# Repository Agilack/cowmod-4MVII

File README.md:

# Cowmod
Cowmod is a family of development boards to help quick prototyping using a
main board and a set of modules. The 4MVII board is focused on PMODs modules
form-factor and offer 4 PMOD connectors to connect extensions.

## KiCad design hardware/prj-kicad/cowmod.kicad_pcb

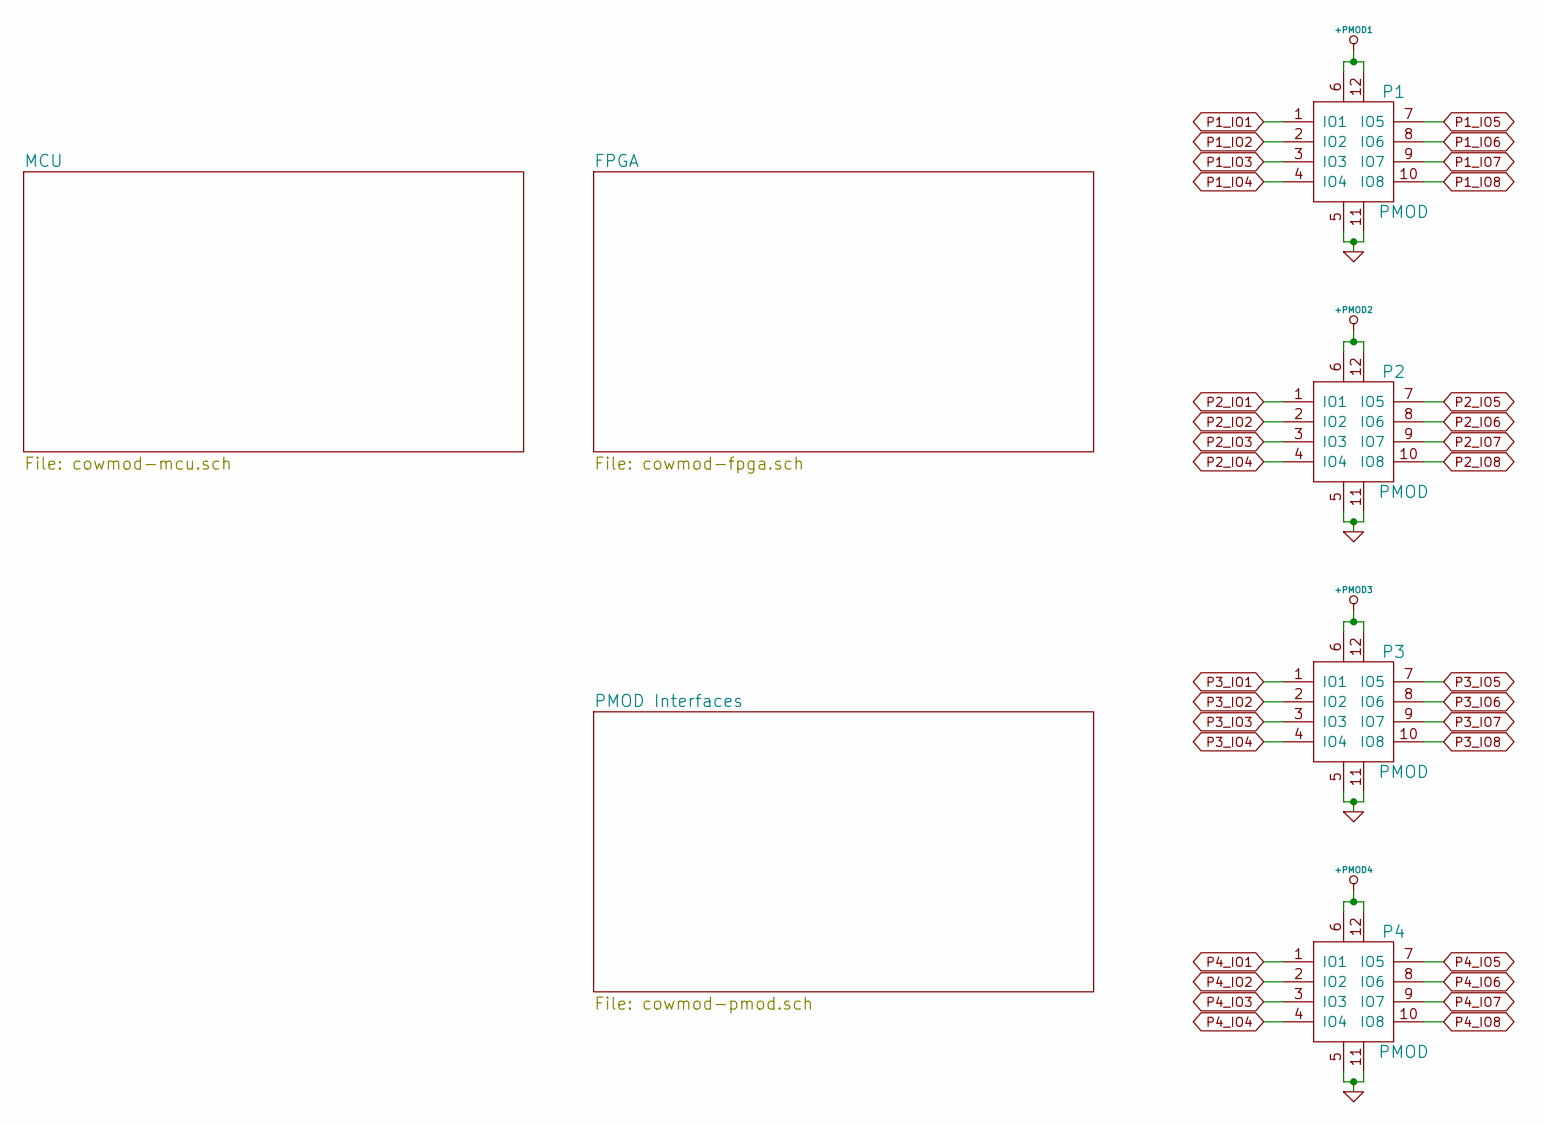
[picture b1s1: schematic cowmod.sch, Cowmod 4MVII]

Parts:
P1, P2, P3, P4: PMOD; PMOD_SSW106-RA

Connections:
+PMOD1: P1.6, P1.12; also elsewhere on the board
+PMOD2: P2.6, P2.12; also elsewhere on the board
+PMOD3: P3.6, P3.12; also elsewhere on the board
+PMOD4: P4.6, P4.12; also elsewhere on the board
GND: P1.5, P1.11, P2.5, P2.11, P3.5, P3.11, P4.5, P4.11; also elsewhere on the board
P1_IO1: P1.1 (IO1); also elsewhere on the board
P1_IO2: P1.2 (IO2); also elsewhere on the board
P1_IO3: P1.3 (IO3); also elsewhere on the board
P1_IO4: P1.4 (IO4); also elsewhere on the board
P1_IO5: P1.7 (IO5); also elsewhere on the board
P1_IO6: P1.8 (IO6); also elsewhere on the board
P1_IO7: P1.9 (IO7); also elsewhere on the board
P1_IO8: P1.10 (IO8); also elsewhere on the board
P2_IO1: P2.1 (IO1); also elsewhere on the board
P2_IO2: P2.2 (IO2); also elsewhere on the board
P2_IO3: P2.3 (IO3); also elsewhere on the board
P2_IO4: P2.4 (IO4); also elsewhere on the board
P2_IO5: P2.7 (IO5); also elsewhere on the board
P2_IO6: P2.8 (IO6); also elsewhere on the board
P2_IO7: P2.9 (IO7); also elsewhere on the board
P2_IO8: P2.10 (IO8); also elsewhere on the board
P3_IO1: P3.1 (IO1); also elsewhere on the board
P3_IO2: P3.2 (IO2); also elsewhere on the board
P3_IO3: P3.3 (IO3); also elsewhere on the board
P3_IO4: P3.4 (IO4); also elsewhere on the board
P3_IO5: P3.7 (IO5); also elsewhere on the board
P3_IO6: P3.8 (IO6); also elsewhere on the board
P3_IO7: P3.9 (IO7); also elsewhere on the board
P3_IO8: P3.10 (IO8); also elsewhere on the board
P4_IO1: P4.1 (IO1); also elsewhere on the board
P4_IO2: P4.2 (IO2); also elsewhere on the board
P4_IO3: P4.3 (IO3); also elsewhere on the board
P4_IO4: P4.4 (IO4); also elsewhere on the board
P4_IO5: P4.7 (IO5); also elsewhere on the board
P4_IO6: P4.8 (IO6); also elsewhere on the board
P4_IO7: P4.9 (IO7); also elsewhere on the board
P4_IO8: P4.10 (IO8); also elsewhere on the board

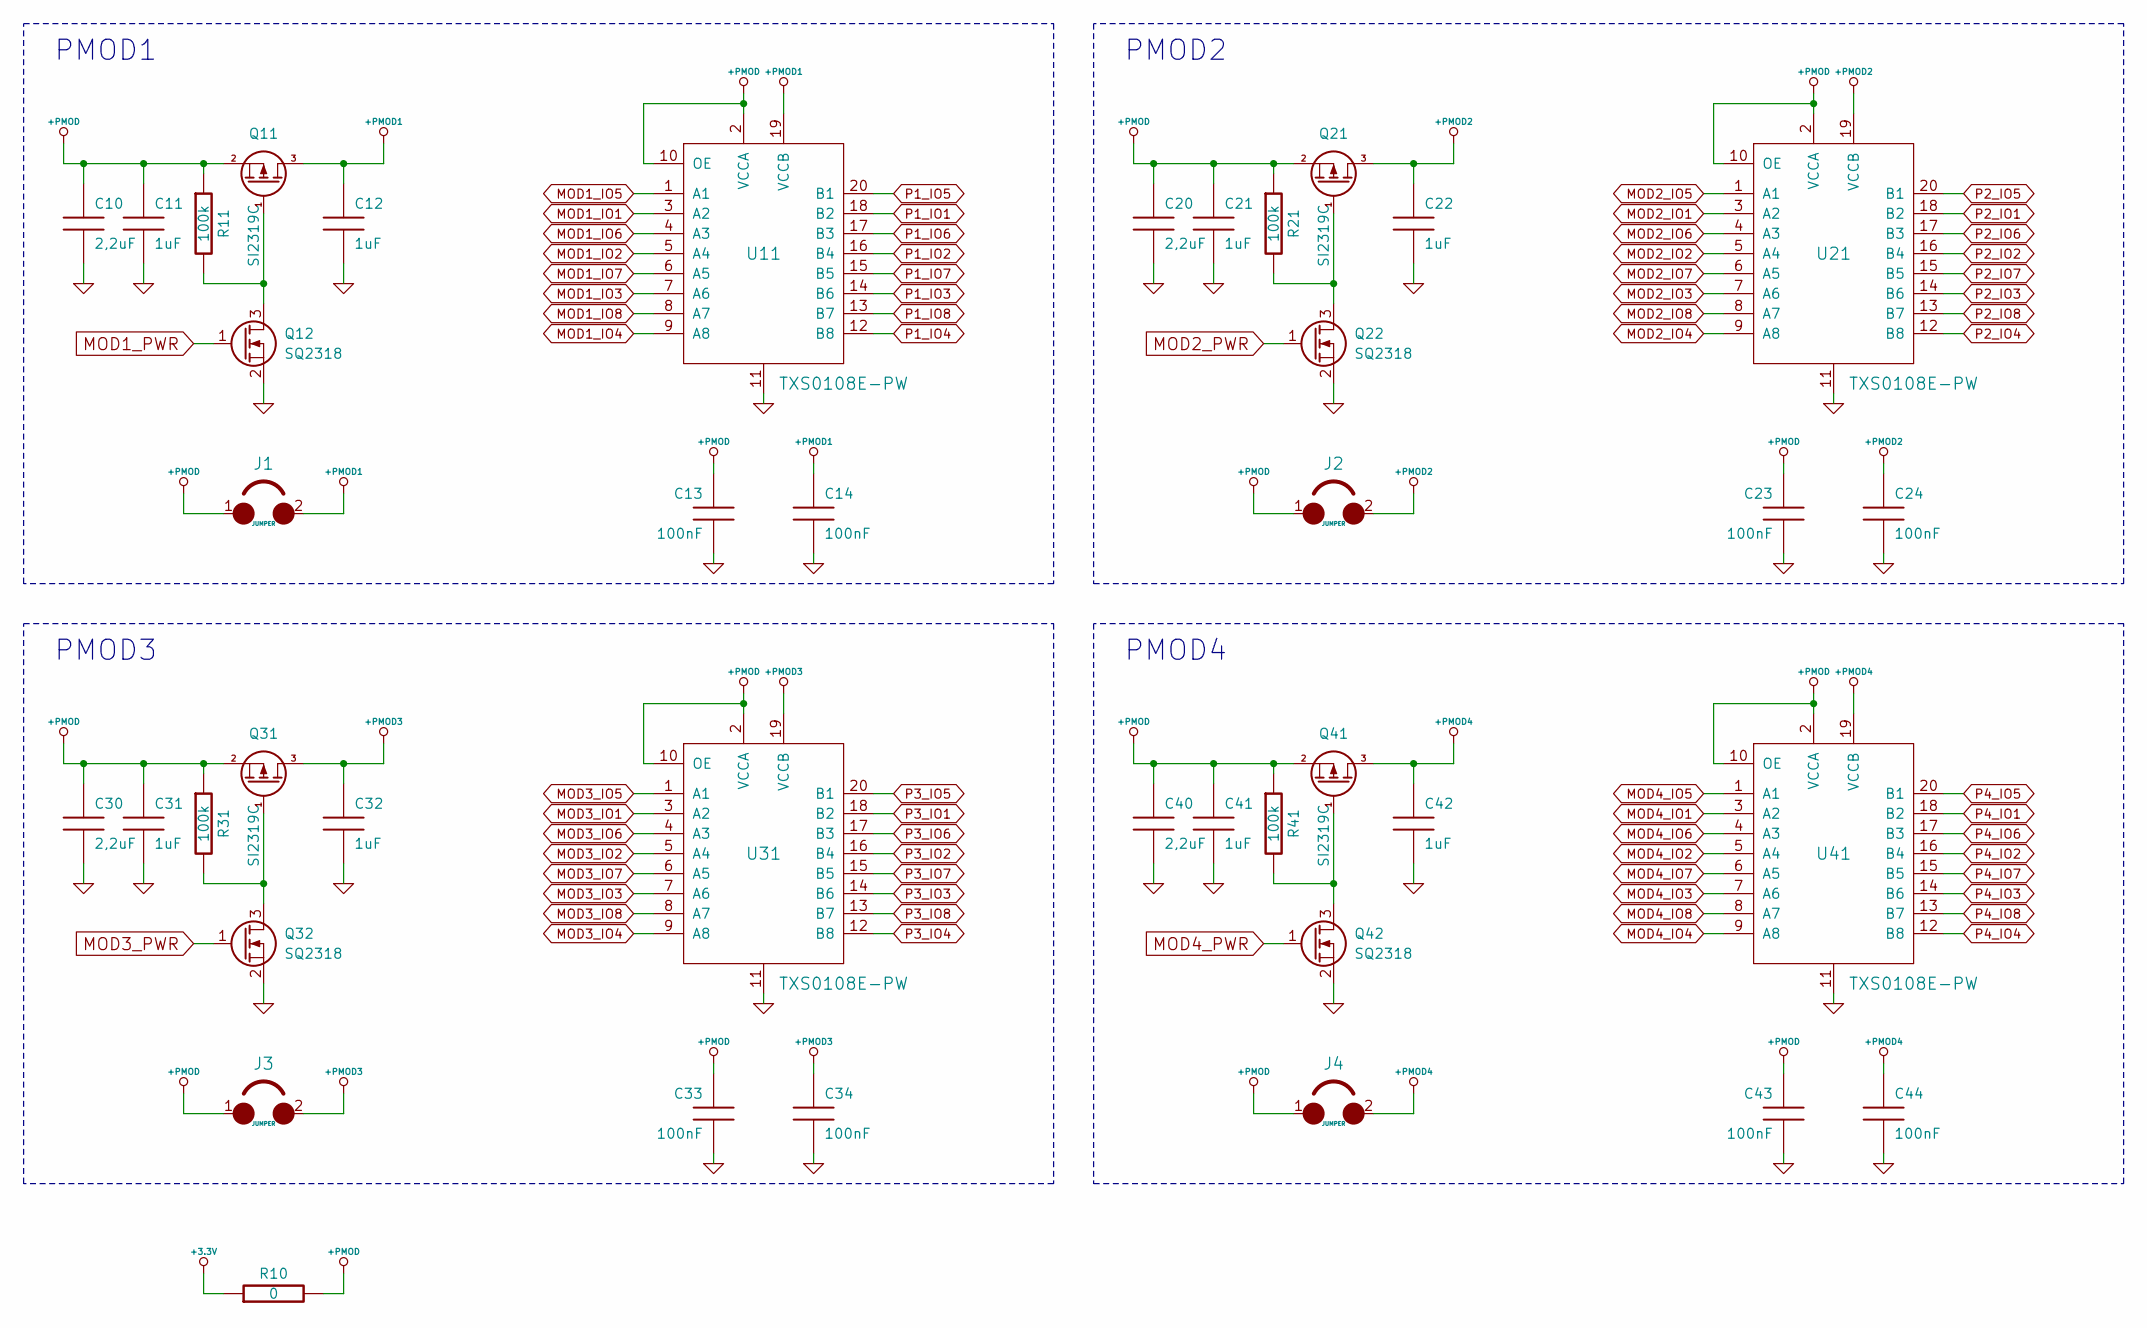
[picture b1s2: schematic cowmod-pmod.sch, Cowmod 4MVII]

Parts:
C10, C20, C30, C40: 2,2uF; SMD1210
C11, C21, C31, C41: 1uF; SMD0603
C12, C22, C32, C42: 1uF; SMD0805
C13, C14, C23, C24, C33, C34, C43, C44: 100nF; SMD0603
J1, J2, J3, J4: JUMPER; CONN_2
Q11, Q21, Q31, Q41: SI2319C; SOT23-3
Q12, Q22, Q32, Q42: SQ2318; SOT23-3
R10: 0; SMD0805
R11, R21, R31, R41: 100k; SMD0603
U11, U21, U31, U41: TXS0108E-PW; TSSOP20

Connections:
+3.3V: R10.1; also elsewhere on the board
+PMOD: C10.1, C11.1, C13.1, C20.1, C21.1, C23.1, C30.1, C31.1, C33.1, C40.1, C41.1, C43.1, J1.1, J2.1, J3.1, J4.1, Q11.2 (S), Q21.2 (S), Q31.2 (S), Q41.2 (S), R10.2, R11.1, R21.1, R31.1, R41.1, U11.2 (VCCA), U11.10 (OE), U21.2 (VCCA), U21.10 (OE), U31.2 (VCCA), U31.10 (OE), U41.2 (VCCA), U41.10 (OE); also elsewhere on the board
+PMOD1: C12.1, C14.1, J1.2, Q11.3 (D), U11.19 (VCCB); also elsewhere on the board
+PMOD2: C22.1, C24.1, J2.2, Q21.3 (D), U21.19 (VCCB); also elsewhere on the board
+PMOD3: C32.1, C34.1, J3.2, Q31.3 (D), U31.19 (VCCB); also elsewhere on the board
+PMOD4: C42.1, C44.1, J4.2, Q41.3 (D), U41.19 (VCCB); also elsewhere on the board
GND: C10.2, C11.2, C12.2, C13.2, C14.2, C20.2, C21.2, C22.2, C23.2, C24.2, C30.2, C31.2, C32.2, C33.2, C34.2, C40.2, C41.2, C42.2, C43.2, C44.2, Q12.2 (S), Q22.2 (S), Q32.2 (S), Q42.2 (S), U11.11, U21.11, U31.11, U41.11; also elsewhere on the board
MOD1_IO1: U11.3 (A2); also elsewhere on the board
MOD1_IO2: U11.5 (A4); also elsewhere on the board
MOD1_IO3: U11.7 (A6); also elsewhere on the board
MOD1_IO4: U11.9 (A8); also elsewhere on the board
MOD1_IO5: U11.1 (A1); also elsewhere on the board
MOD1_IO6: U11.4 (A3); also elsewhere on the board
MOD1_IO7: U11.6 (A5); also elsewhere on the board
MOD1_IO8: U11.8 (A7); also elsewhere on the board
MOD1_PWR: Q12.1 (G)
MOD2_IO1: U21.3 (A2); also elsewhere on the board
MOD2_IO2: U21.5 (A4); also elsewhere on the board
MOD2_IO3: U21.7 (A6); also elsewhere on the board
MOD2_IO4: U21.9 (A8); also elsewhere on the board
MOD2_IO5: U21.1 (A1); also elsewhere on the board
MOD2_IO6: U21.4 (A3); also elsewhere on the board
MOD2_IO7: U21.6 (A5); also elsewhere on the board
MOD2_IO8: U21.8 (A7); also elsewhere on the board
MOD2_PWR: Q22.1 (G)
MOD3_IO1: U31.3 (A2); also elsewhere on the board
MOD3_IO2: U31.5 (A4); also elsewhere on the board
MOD3_IO3: U31.7 (A6); also elsewhere on the board
MOD3_IO4: U31.9 (A8); also elsewhere on the board
MOD3_IO5: U31.1 (A1); also elsewhere on the board
MOD3_IO6: U31.4 (A3); also elsewhere on the board
MOD3_IO7: U31.6 (A5); also elsewhere on the board
MOD3_IO8: U31.8 (A7); also elsewhere on the board
MOD3_PWR: Q32.1 (G)
MOD4_IO1: U41.3 (A2); also elsewhere on the board
MOD4_IO2: U41.5 (A4); also elsewhere on the board
MOD4_IO3: U41.7 (A6); also elsewhere on the board
MOD4_IO4: U41.9 (A8); also elsewhere on the board
MOD4_IO5: U41.1 (A1); also elsewhere on the board
MOD4_IO6: U41.4 (A3); also elsewhere on the board
MOD4_IO7: U41.6 (A5); also elsewhere on the board
MOD4_IO8: U41.8 (A7); also elsewhere on the board
MOD4_PWR: Q42.1 (G)
unnamed: Q11.1 (G), Q12.3 (D), R11.2
unnamed: Q21.1 (G), Q22.3 (D), R21.2
unnamed: Q31.1 (G), Q32.3 (D), R31.2
unnamed: Q41.1 (G), Q42.3 (D), R41.2
P1_IO1: U11.18 (B2); also elsewhere on the board
P1_IO2: U11.16 (B4); also elsewhere on the board
P1_IO3: U11.14 (B6); also elsewhere on the board
P1_IO4: U11.12 (B8); also elsewhere on the board
P1_IO5: U11.20 (B1); also elsewhere on the board
P1_IO6: U11.17 (B3); also elsewhere on the board
P1_IO7: U11.15 (B5); also elsewhere on the board
P1_IO8: U11.13 (B7); also elsewhere on the board
P2_IO1: U21.18 (B2); also elsewhere on the board
P2_IO2: U21.16 (B4); also elsewhere on the board
P2_IO3: U21.14 (B6); also elsewhere on the board
P2_IO4: U21.12 (B8); also elsewhere on the board
P2_IO5: U21.20 (B1); also elsewhere on the board
P2_IO6: U21.17 (B3); also elsewhere on the board
P2_IO7: U21.15 (B5); also elsewhere on the board
P2_IO8: U21.13 (B7); also elsewhere on the board
P3_IO1: U31.18 (B2); also elsewhere on the board
P3_IO2: U31.16 (B4); also elsewhere on the board
P3_IO3: U31.14 (B6); also elsewhere on the board
P3_IO4: U31.12 (B8); also elsewhere on the board
P3_IO5: U31.20 (B1); also elsewhere on the board
P3_IO6: U31.17 (B3); also elsewhere on the board
P3_IO7: U31.15 (B5); also elsewhere on the board
P3_IO8: U31.13 (B7); also elsewhere on the board
P4_IO1: U41.18 (B2); also elsewhere on the board
P4_IO2: U41.16 (B4); also elsewhere on the board
P4_IO3: U41.14 (B6); also elsewhere on the board
P4_IO4: U41.12 (B8); also elsewhere on the board
P4_IO5: U41.20 (B1); also elsewhere on the board
P4_IO6: U41.17 (B3); also elsewhere on the board
P4_IO7: U41.15 (B5); also elsewhere on the board
P4_IO8: U41.13 (B7); also elsewhere on the board

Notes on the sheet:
PMOD1
PMOD2
PMOD3
PMOD4

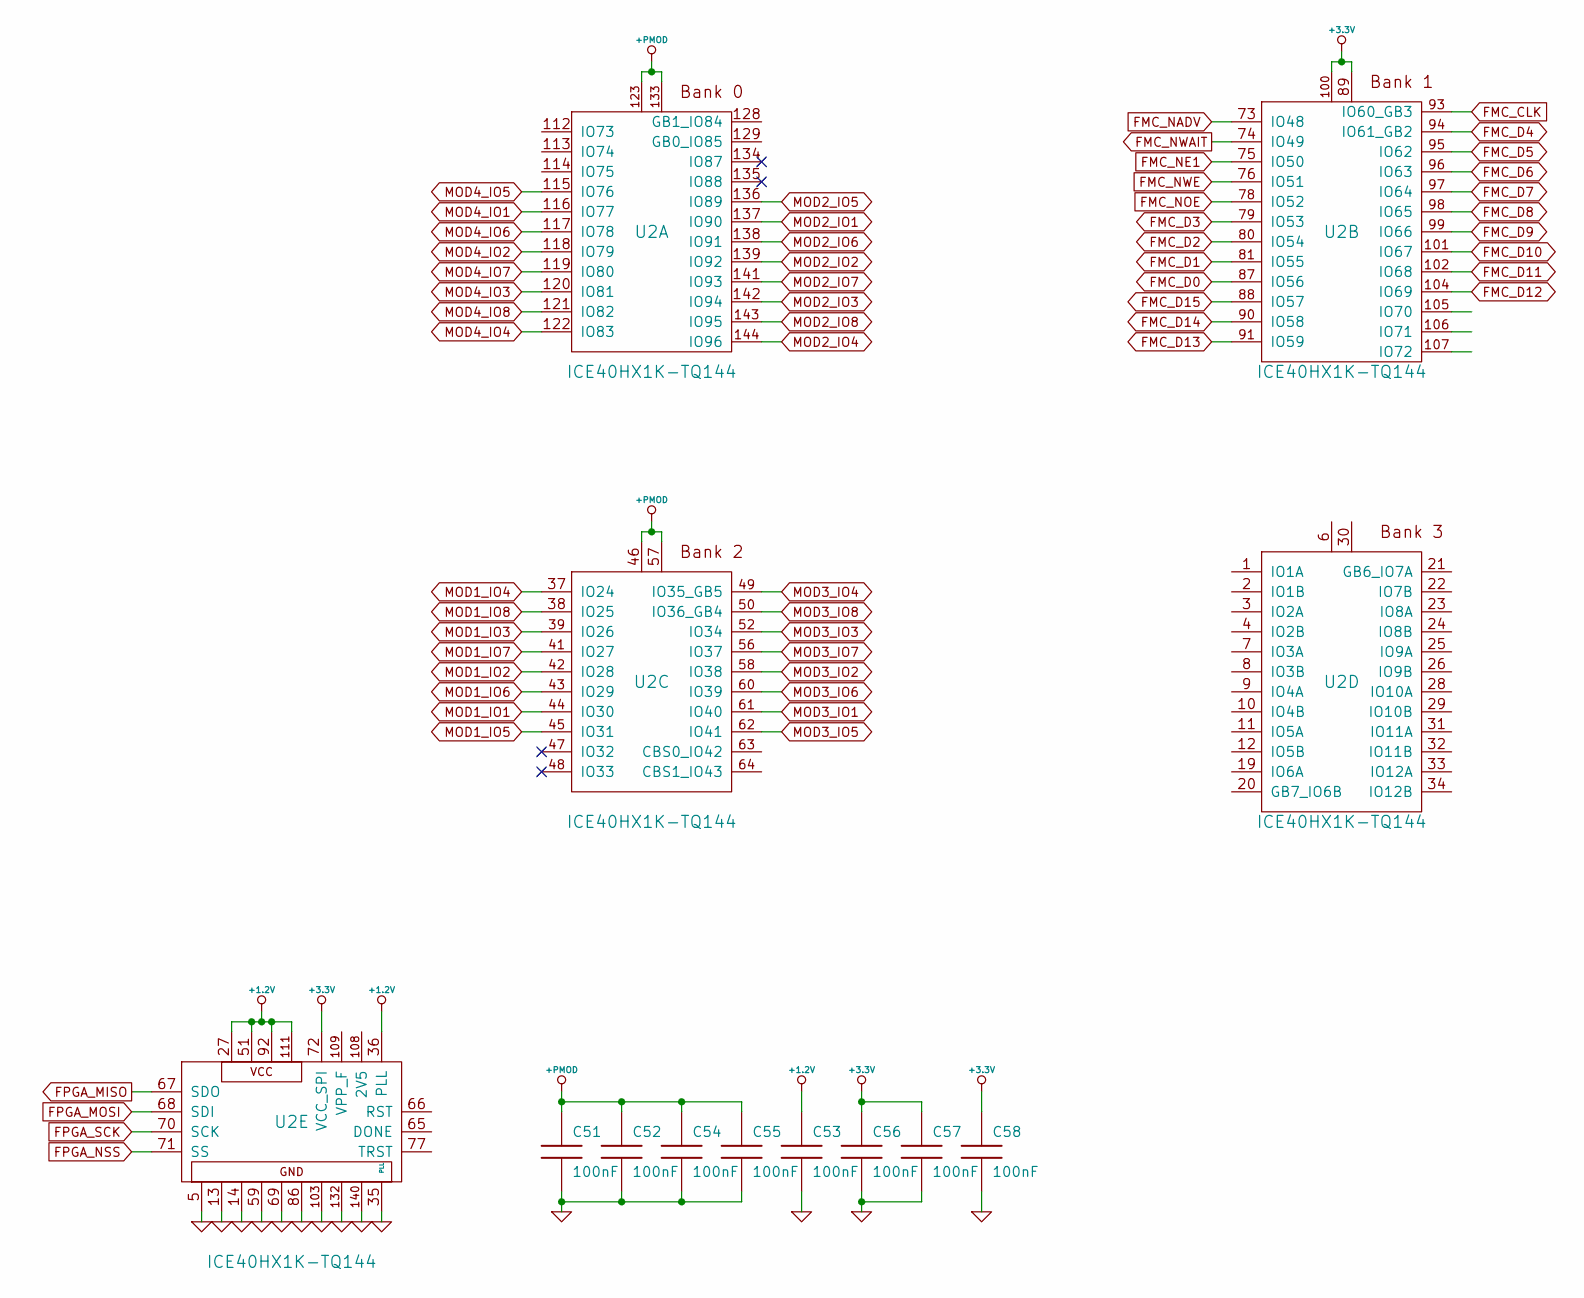
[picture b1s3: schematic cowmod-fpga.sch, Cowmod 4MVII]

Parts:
C51, C52, C53, C54, C55, C56, C57, C58: 100nF; SMD0603
U2: ICE40HX1K-TQ144; TQFP144

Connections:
+1.2V: C53.1, U2.27, U2.36 (PLL), U2.51, U2.92, U2.111
+3.3V: C56.1, C57.1, C58.1, U2.72 (VCC_SPI), U2.89, U2.100; also elsewhere on the board
+PMOD: C51.1, C52.1, C54.1, C55.1, U2.46, U2.57, U2.123, U2.133; also elsewhere on the board
FMC_CLK: U2.93 (IO60_GB3); also elsewhere on the board
FMC_D0: U2.87 (IO56); also elsewhere on the board
FMC_D1: U2.81 (IO55); also elsewhere on the board
FMC_D2: U2.80 (IO54); also elsewhere on the board
FMC_D3: U2.79 (IO53); also elsewhere on the board
FMC_D4: U2.94 (IO61_GB2); also elsewhere on the board
FMC_D5: U2.95 (IO62); also elsewhere on the board
FMC_D6: U2.96 (IO63); also elsewhere on the board
FMC_D7: U2.97 (IO64); also elsewhere on the board
FMC_D8: U2.98 (IO65); also elsewhere on the board
FMC_D9: U2.99 (IO66); also elsewhere on the board
FMC_D10: U2.101 (IO67); also elsewhere on the board
FMC_D11: U2.102 (IO68); also elsewhere on the board
FMC_D12: U2.104 (IO69); also elsewhere on the board
FMC_D13: U2.91 (IO59); also elsewhere on the board
FMC_D14: U2.90 (IO58); also elsewhere on the board
FMC_D15: U2.88 (IO57); also elsewhere on the board
FMC_NADV: U2.73 (IO48); also elsewhere on the board
FMC_NE1: U2.75 (IO50); also elsewhere on the board
FMC_NOE: U2.78 (IO52); also elsewhere on the board
FMC_NWAIT: U2.74 (IO49); also elsewhere on the board
FMC_NWE: U2.76 (IO51); also elsewhere on the board
FPGA_MISO: U2.67 (SDO); also elsewhere on the board
FPGA_MOSI: U2.68 (SDI); also elsewhere on the board
FPGA_NSS: U2.71 (SS); also elsewhere on the board
FPGA_SCK: U2.70 (SCK); also elsewhere on the board
GND: C51.2, C52.2, C53.2, C54.2, C55.2, C56.2, C57.2, C58.2, U2.5, U2.13, U2.14, U2.35 (PLL), U2.59, U2.69, U2.86, U2.103, U2.132, U2.140; also elsewhere on the board
MOD1_IO1: U2.44 (IO30); also elsewhere on the board
MOD1_IO2: U2.42 (IO28); also elsewhere on the board
MOD1_IO3: U2.39 (IO26); also elsewhere on the board
MOD1_IO4: U2.37 (IO24); also elsewhere on the board
MOD1_IO5: U2.45 (IO31); also elsewhere on the board
MOD1_IO6: U2.43 (IO29); also elsewhere on the board
MOD1_IO7: U2.41 (IO27); also elsewhere on the board
MOD1_IO8: U2.38 (IO25); also elsewhere on the board
MOD2_IO1: U2.137 (IO90); also elsewhere on the board
MOD2_IO2: U2.139 (IO92); also elsewhere on the board
MOD2_IO3: U2.142 (IO94); also elsewhere on the board
MOD2_IO4: U2.144 (IO96); also elsewhere on the board
MOD2_IO5: U2.136 (IO89); also elsewhere on the board
MOD2_IO6: U2.138 (IO91); also elsewhere on the board
MOD2_IO7: U2.141 (IO93); also elsewhere on the board
MOD2_IO8: U2.143 (IO95); also elsewhere on the board
MOD3_IO1: U2.61 (IO40); also elsewhere on the board
MOD3_IO2: U2.58 (IO38); also elsewhere on the board
MOD3_IO3: U2.52 (IO34); also elsewhere on the board
MOD3_IO4: U2.49 (IO35_GB5); also elsewhere on the board
MOD3_IO5: U2.62 (IO41); also elsewhere on the board
MOD3_IO6: U2.60 (IO39); also elsewhere on the board
MOD3_IO7: U2.56 (IO37); also elsewhere on the board
MOD3_IO8: U2.50 (IO36_GB4); also elsewhere on the board
MOD4_IO1: U2.116 (IO77); also elsewhere on the board
MOD4_IO2: U2.118 (IO79); also elsewhere on the board
MOD4_IO3: U2.120 (IO81); also elsewhere on the board
MOD4_IO4: U2.122 (IO83); also elsewhere on the board
MOD4_IO5: U2.115 (IO76); also elsewhere on the board
MOD4_IO6: U2.117 (IO78); also elsewhere on the board
MOD4_IO7: U2.119 (IO80); also elsewhere on the board
MOD4_IO8: U2.121 (IO82); also elsewhere on the board

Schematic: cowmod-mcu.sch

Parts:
C60, C61: 2,2uF; SMD0603
C63, C64, C65: 100nF; SMD0603
R1: 10k
U1: STM32F745ZX; TQFP144

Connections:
+3.3V: C63.1, C64.1, C65.1, U1.17, U1.30, U1.39, U1.52, U1.62, U1.72, U1.84, U1.95, U1.108, U1.121, U1.131, U1.144; also elsewhere on the board
FMC_CLK: U1.117; also elsewhere on the board
FMC_D0: U1.85; also elsewhere on the board
FMC_D1: U1.86; also elsewhere on the board
FMC_D2: U1.114; also elsewhere on the board
FMC_D3: U1.115; also elsewhere on the board
FMC_D4: U1.58; also elsewhere on the board
FMC_D5: U1.59; also elsewhere on the board
FMC_D6: U1.60; also elsewhere on the board
FMC_D7: U1.63; also elsewhere on the board
FMC_D8: U1.64; also elsewhere on the board
FMC_D9: U1.65; also elsewhere on the board
FMC_D10: U1.66; also elsewhere on the board
FMC_D11: U1.67; also elsewhere on the board
FMC_D12: U1.68; also elsewhere on the board
FMC_D13: U1.77; also elsewhere on the board
FMC_D14: U1.78; also elsewhere on the board
FMC_D15: U1.79; also elsewhere on the board
FMC_NADV: U1.137; also elsewhere on the board
FMC_NE1: U1.123; also elsewhere on the board
FMC_NOE: U1.118; also elsewhere on the board
FMC_NWAIT: U1.122; also elsewhere on the board
FMC_NWE: U1.119; also elsewhere on the board
FPGA_MISO: U1.112; also elsewhere on the board
FPGA_MOSI: U1.113; also elsewhere on the board
FPGA_NSS: U1.110; also elsewhere on the board
FPGA_SCK: U1.111; also elsewhere on the board
GND: C60.2, C61.2, C63.2, C64.2, C65.2, R1.2, U1.16, U1.31, U1.38, U1.51, U1.61, U1.83, U1.94, U1.107, U1.120, U1.130; also elsewhere on the board
MCU_RST: U1.25
unnamed: C60.1, U1.106
unnamed: C61.1, U1.71

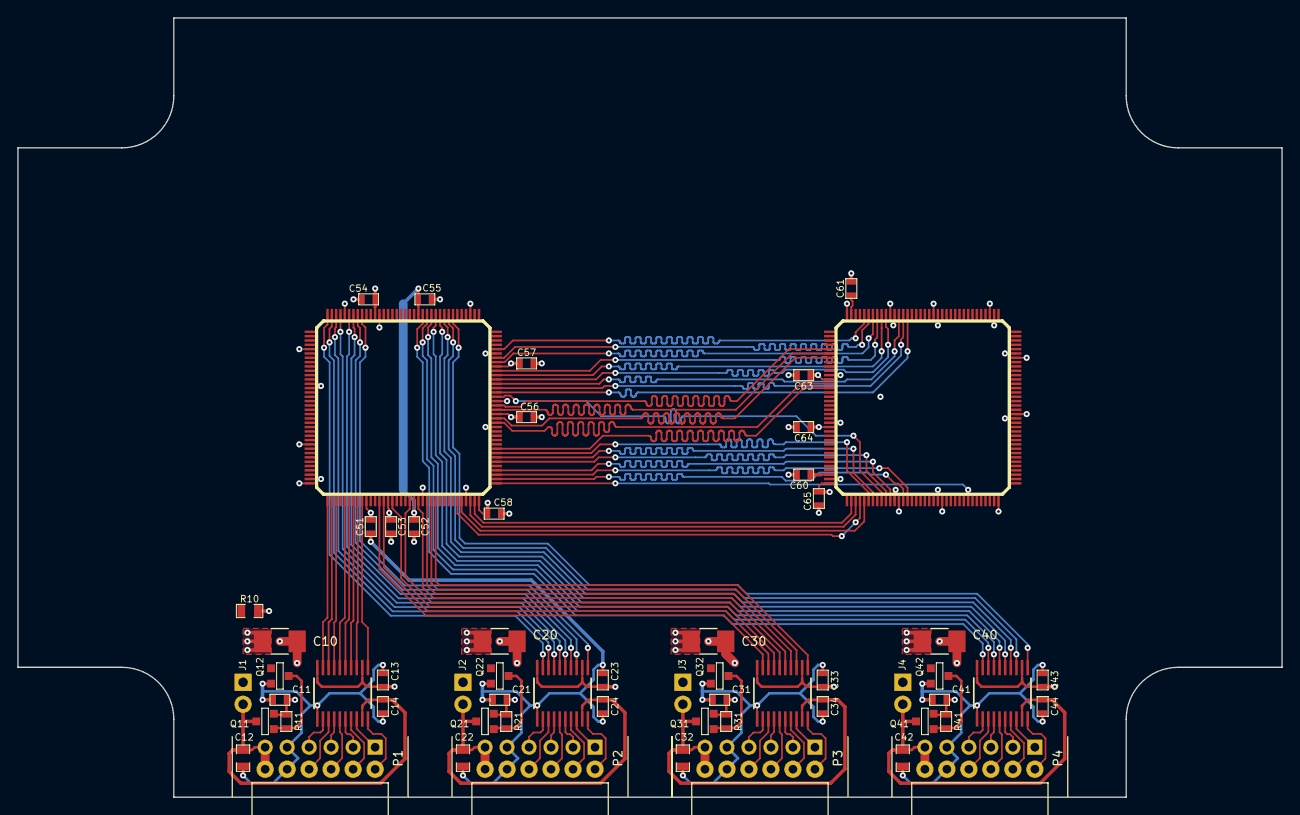
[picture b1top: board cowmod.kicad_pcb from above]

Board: 4 copper layers, 146.0 x 90.0 mm, 60 parts (0 on the bottom side), 104 nets.

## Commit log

2019-05-29 --=={ Initial Commit }==-- Create project, add board squeleton
2019-05-30 = ADD: Insert connectors for PMOD modules and buffer/power of the first one
2019-06-03 = ADD: Insert FPGA and route all PMOD ports
2019-06-04 = ADD: Insert main MCU (STM32) and connect it to FPGA
